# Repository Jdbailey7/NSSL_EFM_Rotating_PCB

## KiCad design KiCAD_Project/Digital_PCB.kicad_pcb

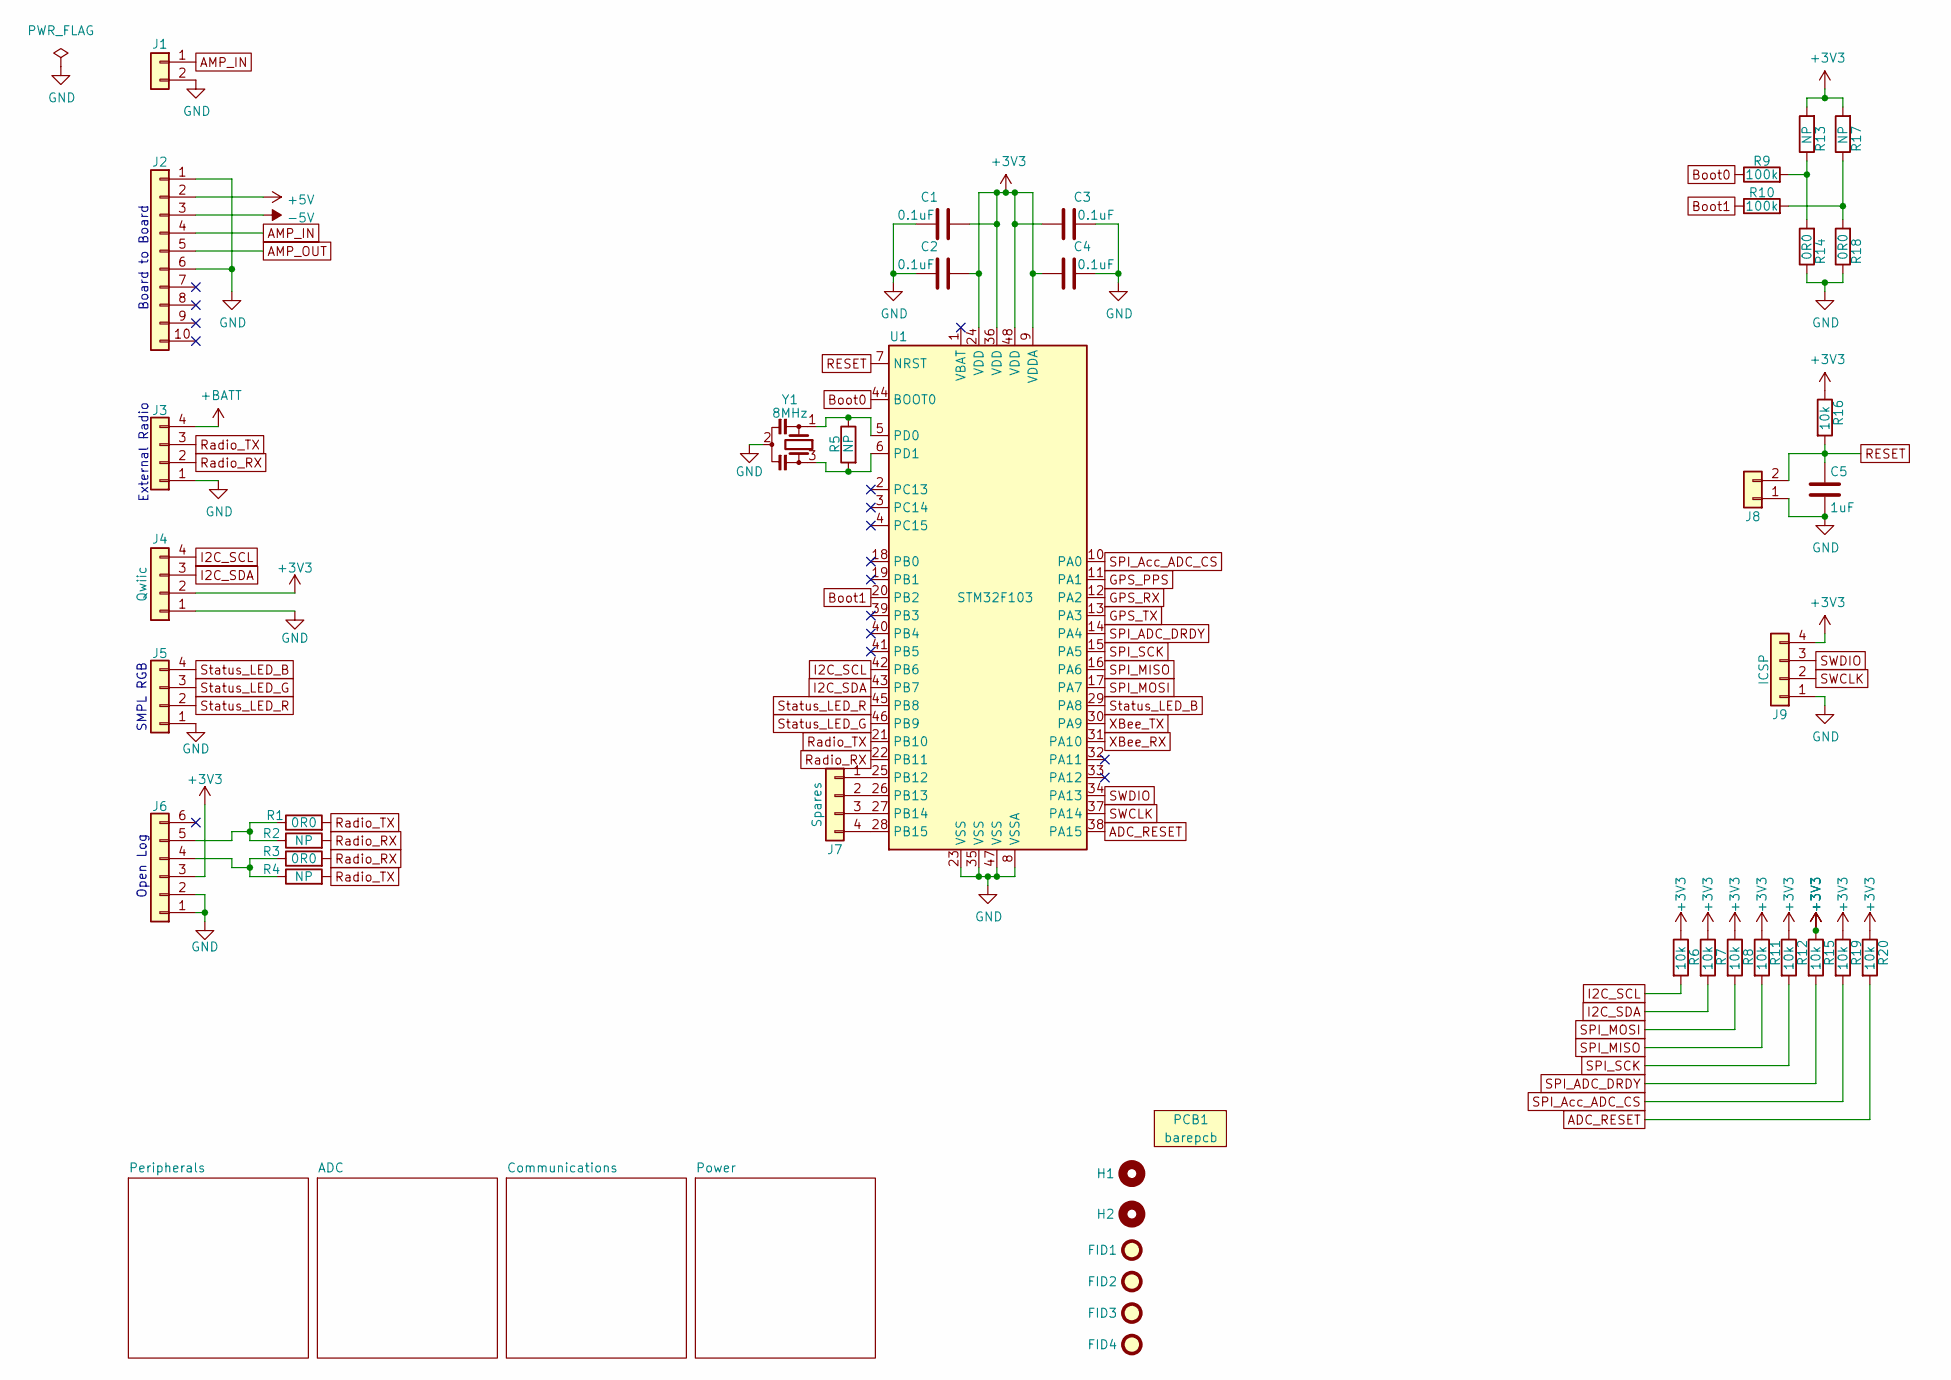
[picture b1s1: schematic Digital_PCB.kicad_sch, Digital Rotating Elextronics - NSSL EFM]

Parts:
C1, C2, C3, C4: 1-0000007
C5: 1-0000018
FID1, FID2, FID3, FID4: Fiducial_1mm_2mm; Fiducial_1mm_Mask2mm
H1, H2: Imperial6; MountingHole_imperial6
J1: NP_Conn_01x02_Relief; SolderWire_1x02_Relief
J2: Board to Board; PinHeader_1x10_P2.54mm_Vertical
J3, J5: 1-0001156
J4: 1-0001205
J6: NP_Conn_01x06; PinHeader_1x06_P2.54mm_Vertical
J7, J9: NP_Conn_01x04; PinHeader_1x04_P2.54mm_Vertical
J8: NP_Conn_01x02_Relief; PinHeader_1x02_P2.54mm_Vertical
PCB1: barepcb
R1, R2, R3, R4, R5, R13, R14, R17, R18: 1-0000006
R6, R7, R8, R11, R12, R15, R16, R19, R20: 1-0000010
R9, R10: 1-0000174
U1: 1-0000207
Y1: 1-0000721

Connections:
+3V3: C1.2, C2.2, C3.2, C4.2, J4.2, J6.3, J9.4, R6.1, R7.1, R8.1, R11.1, R12.1, R13.2, R15.1, R16.1, R17.2, R19.1, R20.1, U1.9 (VDDA), U1.24 (VDD), U1.36 (VDD), U1.48 (VDD); also elsewhere on the board
+5V: J2.2; also elsewhere on the board
+BATT: J3.4; also elsewhere on the board
-5V: J2.3; also elsewhere on the board
ADC_RESET: R20.2, U1.38 (PA15); also elsewhere on the board
AMP_IN: J1.1, J2.4
AMP_OUT: J2.5; also elsewhere on the board
Boot0: R9.1, U1.44 (BOOT0)
Boot1: R10.1, U1.20 (PB2)
GND: C1.1, C2.1, C3.1, C4.1, C5.2, J1.2, J2.1, J2.6, J3.1, J4.1, J5.1, J6.1, J6.2, J8.1, J9.1, R14.1, R18.1, U1.8 (VSSA), U1.23 (VSS), U1.35 (VSS), U1.47 (VSS), Y1.2; also elsewhere on the board
GPS_PPS: U1.11 (PA1); also elsewhere on the board
GPS_RX: U1.12 (PA2); also elsewhere on the board
GPS_TX: U1.13 (PA3); also elsewhere on the board
I2C_SCL: J4.4, R6.2, U1.42 (PB6); also elsewhere on the board
I2C_SDA: J4.3, R7.2, U1.43 (PB7); also elsewhere on the board
unnamed: J6.4, R3.1, R4.1
unnamed: J6.5, R1.1, R2.1
unnamed: J7.1, U1.25 (PB12)
unnamed: J7.2, U1.26 (PB13)
unnamed: J7.3, U1.27 (PB14)
unnamed: J7.4, U1.28 (PB15)
unnamed: R10.2, R17.1, R18.2
unnamed: R9.2, R13.1, R14.2
unnamed: R5.1, U1.5 (PD0), Y1.1
unnamed: R5.2, U1.6 (PD1), Y1.3
RESET: C5.1, J8.2, R16.2, U1.7 (NRST); also elsewhere on the board
Radio_RX: J3.2, R2.2, R3.2, U1.22 (PB11)
Radio_TX: J3.3, R1.2, R4.2, U1.21 (PB10)
SPI_ADC_DRDY: R15.2, U1.14 (PA4); also elsewhere on the board
SPI_Acc_ADC_CS: R19.2, U1.10 (PA0); also elsewhere on the board
SPI_MISO: R11.2, U1.16 (PA6); also elsewhere on the board
SPI_MOSI: R8.2, U1.17 (PA7); also elsewhere on the board
SPI_SCK: R12.2, U1.15 (PA5); also elsewhere on the board
SWCLK: J9.2, U1.37 (PA14)
SWDIO: J9.3, U1.34 (PA13)
Status_LED_B: J5.4, U1.29 (PA8)
Status_LED_G: J5.3, U1.46 (PB9)
Status_LED_R: J5.2, U1.45 (PB8)
XBee_RX: U1.31 (PA10); also elsewhere on the board
XBee_TX: U1.30 (PA9); also elsewhere on the board

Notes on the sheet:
Board to Board
External Radio
Open Log
SMPL RGB

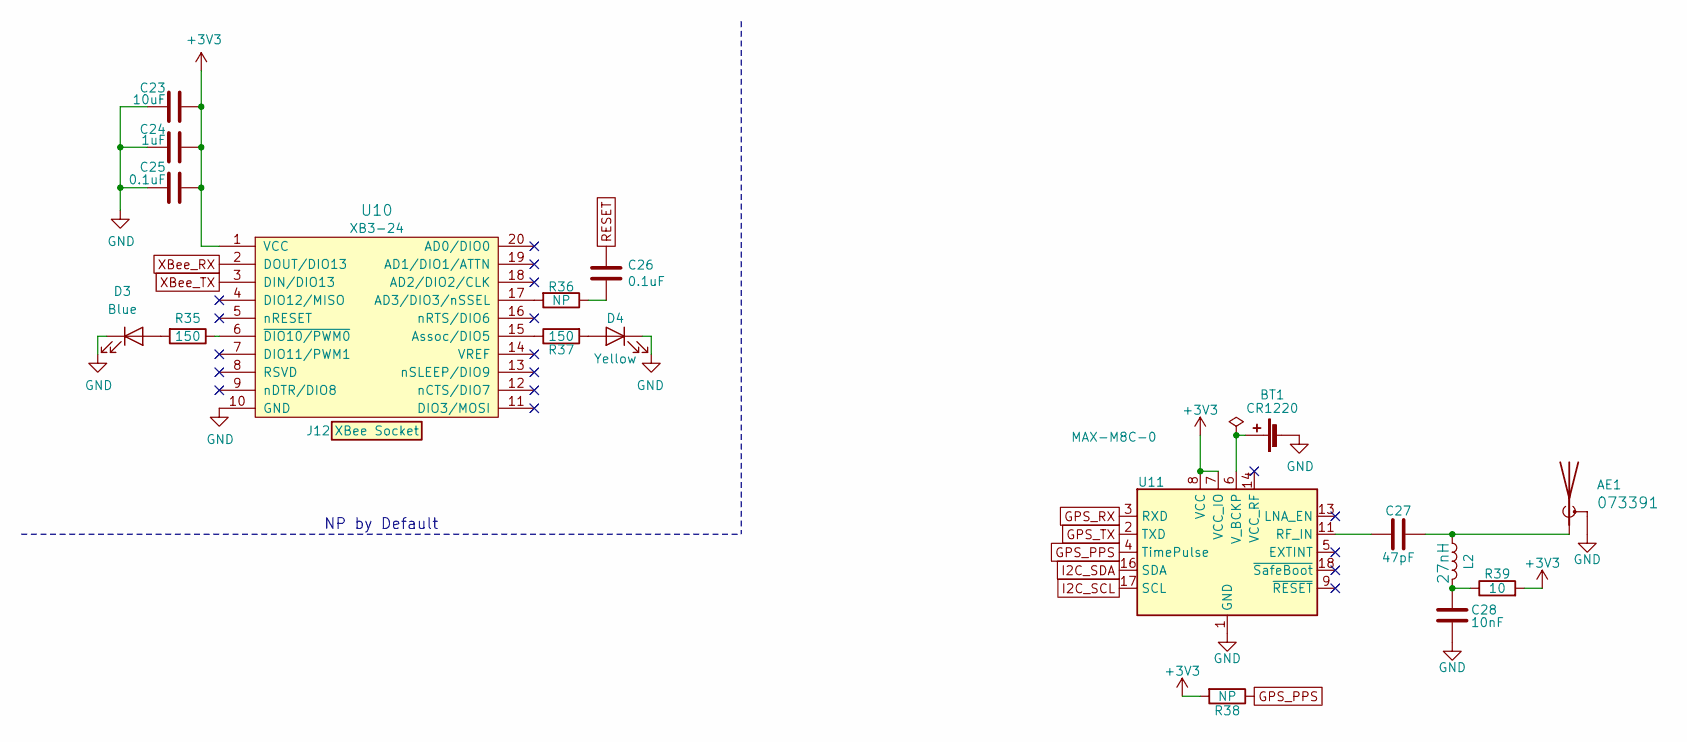
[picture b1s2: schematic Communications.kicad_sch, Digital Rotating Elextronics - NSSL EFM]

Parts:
AE1: 1-0000461
BT1: 1-0000246
C23: 1-0000075
C24: 1-0000018
C25, C26: 1-0000007
C27: 1-0000458
C28: 1-0000014
D3: 1-0000599
D4: 1-0000601
J12: 1-0000050
L2: 1-0000459
R35, R37: 1-0000008
R36: 1-0000006
R38: 1-0000010
R39: 1-0000678
U10: 1-0000785
U11: 1-0000464

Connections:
+3V3: C23.1, C24.1, C25.1, R38.2, R39.2, U10.1 (VCC), U11.7 (VCC_IO), U11.8 (VCC); also elsewhere on the board
GND: AE1.2 (Shield), BT1.2 (-), C23.2, C24.2, C25.2, C28.2, D3.1 (K), D4.1 (K), U10.10 (GND), U11.1 (GND), U11.10 (GND), U11.12 (GND); also elsewhere on the board
GPS_PPS: R38.1, U11.4 (TimePulse); also elsewhere on the board
GPS_RX: U11.3 (RXD); also elsewhere on the board
GPS_TX: U11.2 (TXD); also elsewhere on the board
I2C_SCL: U11.17 (SCL); also elsewhere on the board
I2C_SDA: U11.16 (SDA); also elsewhere on the board
unnamed: AE1.1 (A), C27.2, L2.1
unnamed: BT1.1 (+), U11.6 (V_BCKP)
unnamed: C26.2, R36.1
unnamed: C28.1, L2.2, R39.1
unnamed: D3.2 (A), R35.2
unnamed: D4.2 (A), R37.2
unnamed: R36.2, U10.17 (AD3/DIO3/nSSEL)
unnamed: R37.1, U10.15 (Assoc/DIO5)
unnamed: R35.1, U10.6 (~DIO10/PWM0)
unnamed: C27.1, U11.11 (RF_IN)
RESET: C26.1; also elsewhere on the board
XBee_RX: U10.2 (DOUT/DIO13); also elsewhere on the board
XBee_TX: U10.3 (DIN/DIO13); also elsewhere on the board

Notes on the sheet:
NP by Default

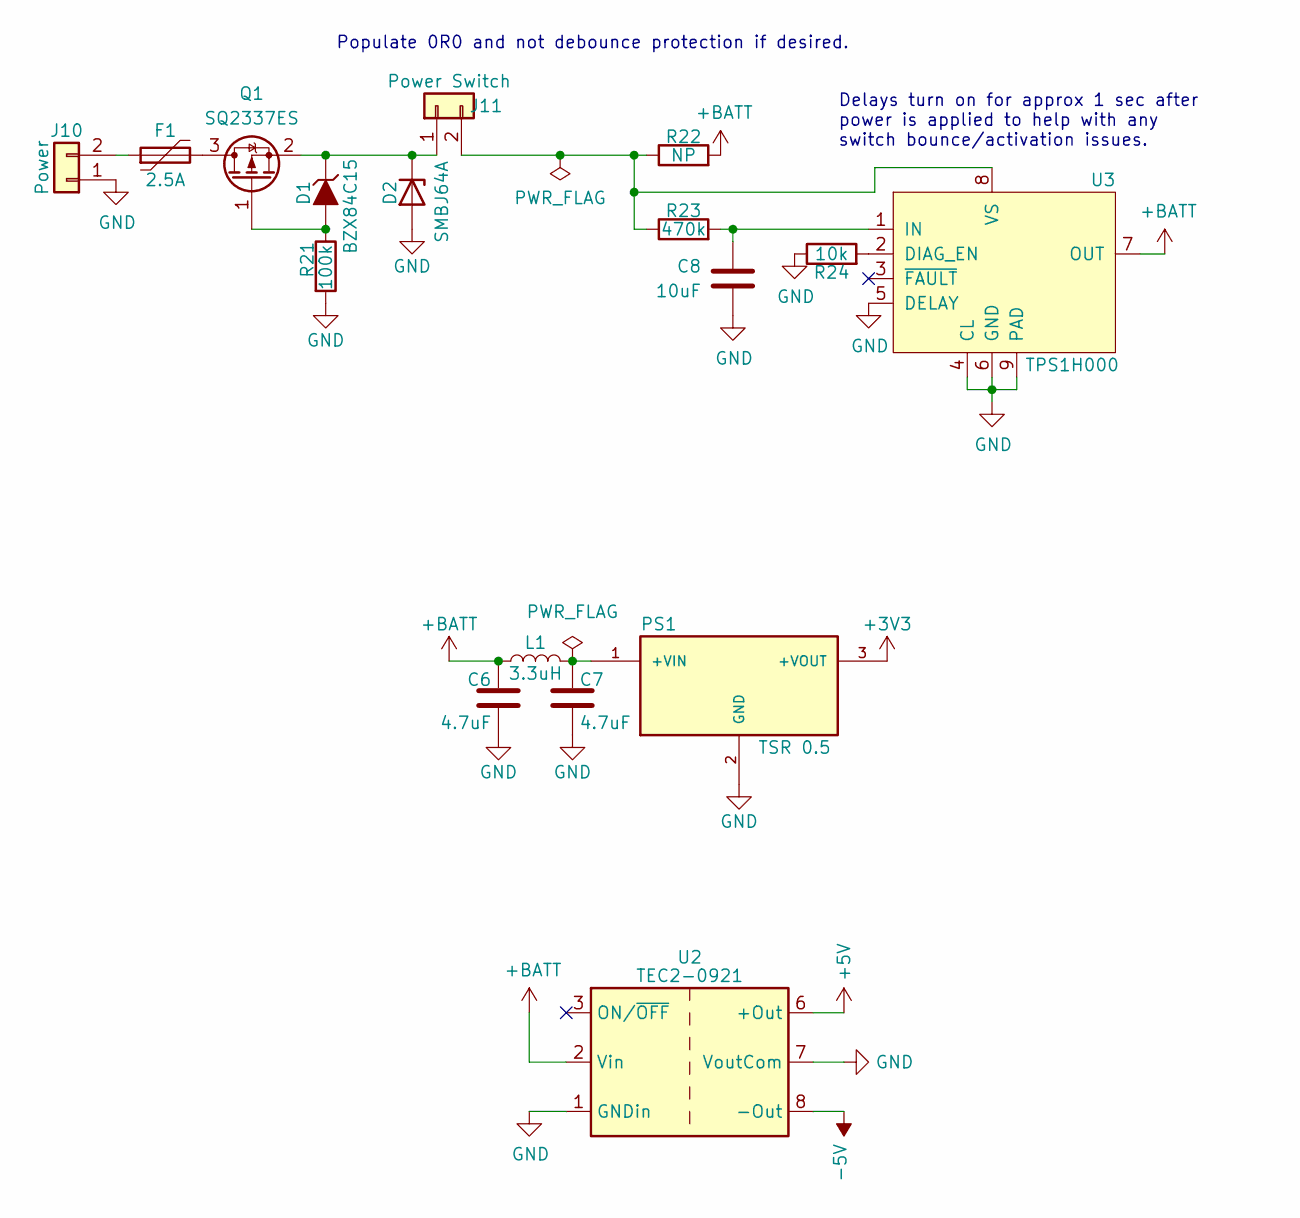
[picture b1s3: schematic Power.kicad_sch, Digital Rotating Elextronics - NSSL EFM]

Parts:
C6, C7: 1-0000136
C8: 1-0000075
D1: 1-0001672
D2: 1-0001537
F1: 1-0000269
J10, J11: NP_Conn_01x02_Relief; SolderWire_1x02_Relief
L1: 1-0000931
PS1: 1-0000727
Q1: 1-0001670
R21: 1-0000174
R22: 1-0000006
R23: 1-0000068
R24: 1-0000010
U2: 1-0000465
U3: 1-0000576

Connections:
+3V3: PS1.3 (+VOUT); also elsewhere on the board
+5V: U2.6 (+Out); also elsewhere on the board
+BATT: C6.1, L1.1, R22.2, U2.2 (Vin), U3.7 (OUT); also elsewhere on the board
-5V: U2.8 (-Out); also elsewhere on the board
GND: C6.2, C7.2, C8.1, D2.2 (A), J10.1, PS1.2 (GND), R21.2, R24.1, U2.1 (GNDin), U2.7 (VoutCom), U3.4 (CL), U3.5 (DELAY), U3.6 (GND), U3.9 (PAD); also elsewhere on the board
unnamed: D1.1 (A), Q1.1 (G), R21.1
unnamed: D1.3 (K), D2.1 (K), J11.1, Q1.2 (S)
unnamed: F1.1, J10.2
unnamed: J11.2, R22.1, R23.1, U3.8 (VS)
unnamed: C7.1, L1.2, PS1.1 (+VIN)
unnamed: F1.2, Q1.3 (D)
unnamed: R24.2, U3.2 (DIAG_EN)
unnamed: C8.2, R23.2, U3.1 (IN)

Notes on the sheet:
Populate 0R0 and not debounce protection if desired.
Delays turn on for approx 1 sec after power is applied to help with any switch bounce/activation issues.

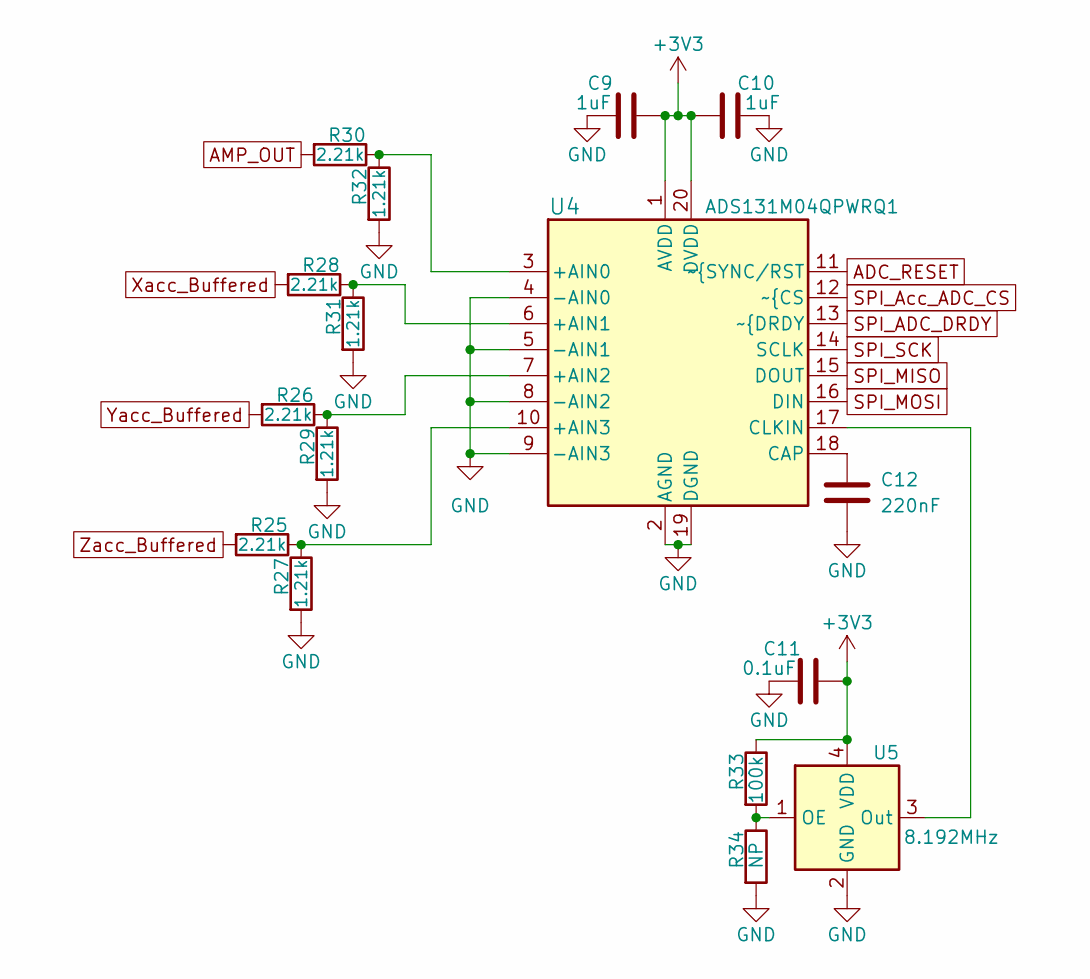
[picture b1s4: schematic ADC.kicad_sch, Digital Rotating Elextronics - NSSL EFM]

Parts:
C9, C10: 1-0000018
C11: 1-0000007
C12: 1-0000926
R25, R26, R28, R30: 1-0001551
R27, R29, R31, R32: 1-0001553
R33: 1-0000174
R34: 1-0000006
U4: 1-0001530
U5: 1-0001542

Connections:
+3V3: C9.1, C10.1, C11.2, R33.1, U4.1 (AVDD), U4.20 (DVDD), U5.4 (VDD); also elsewhere on the board
ADC_RESET: U4.11 (~{SYNC/RST); also elsewhere on the board
AMP_OUT: R30.2; also elsewhere on the board
GND: C9.2, C10.2, C11.1, C12.2, R27.2, R29.2, R31.2, R32.2, R34.2, U4.2 (AGND), U4.4 (-AIN0), U4.5 (-AIN1), U4.8 (-AIN2), U4.9 (-AIN3), U4.19 (DGND), U5.2 (GND); also elsewhere on the board
unnamed: R30.1, R32.1, U4.3 (+AIN0)
unnamed: R28.1, R31.1, U4.6 (+AIN1)
unnamed: R26.1, R29.1, U4.7 (+AIN2)
unnamed: R25.1, R27.1, U4.10 (+AIN3)
unnamed: C12.1, U4.18 (CAP)
unnamed: U4.17 (CLKIN), U5.3 (Out)
unnamed: R33.2, R34.1, U5.1 (OE)
SPI_ADC_DRDY: U4.13 (~{DRDY); also elsewhere on the board
SPI_Acc_ADC_CS: U4.12 (~{CS); also elsewhere on the board
SPI_MISO: U4.15 (DOUT); also elsewhere on the board
SPI_MOSI: U4.16 (DIN); also elsewhere on the board
SPI_SCK: U4.14 (SCLK); also elsewhere on the board
Xacc_Buffered: R28.2; also elsewhere on the board
Yacc_Buffered: R26.2; also elsewhere on the board
Zacc_Buffered: R25.2; also elsewhere on the board

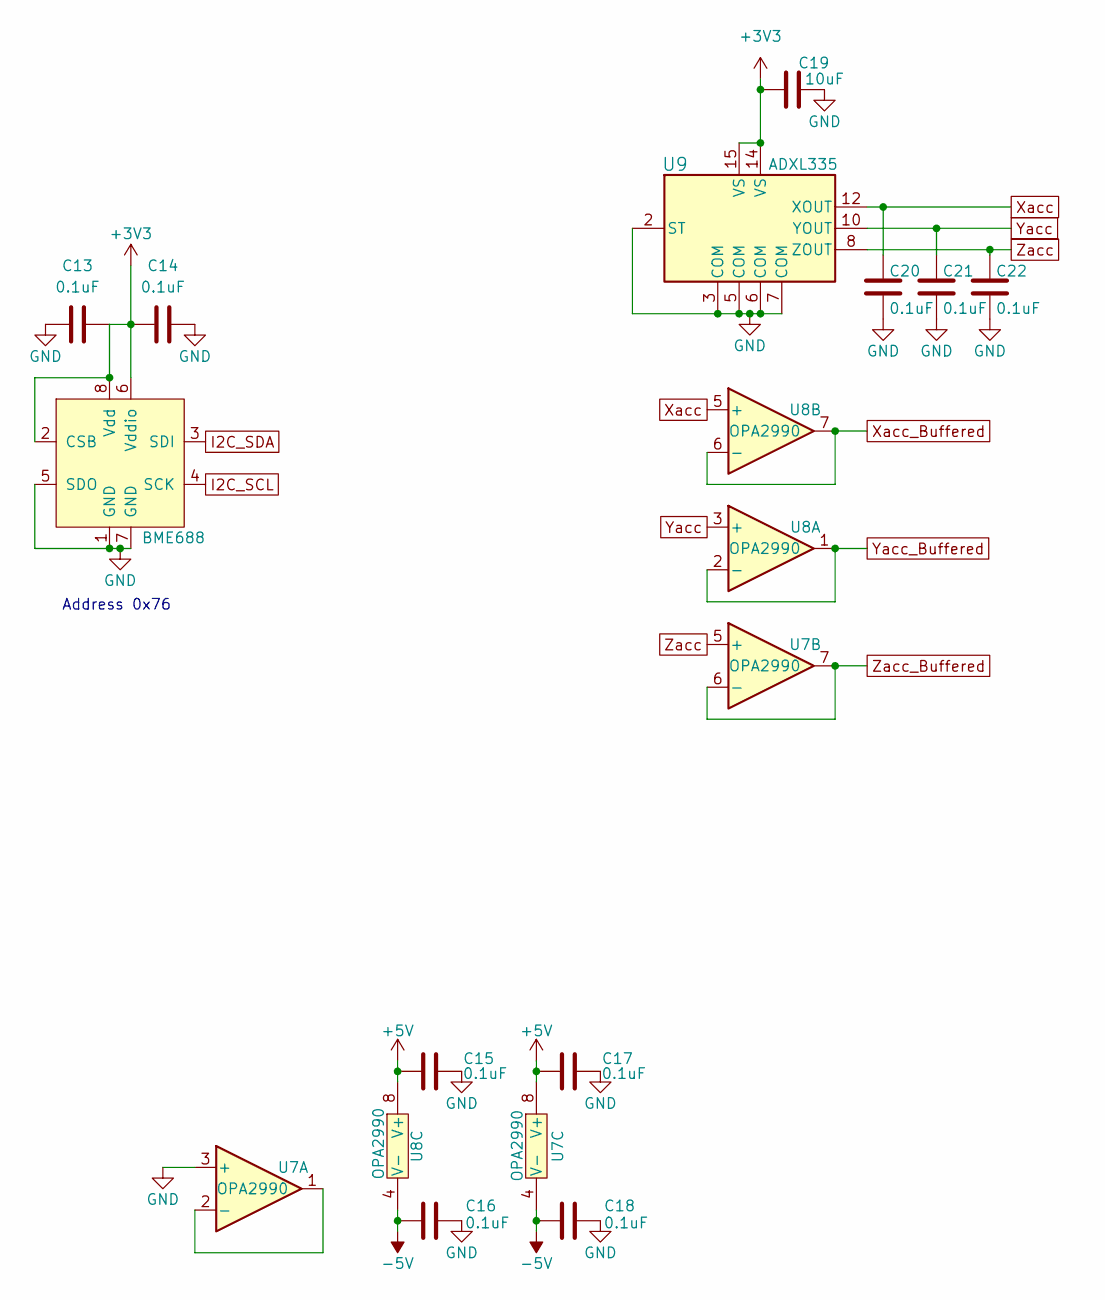
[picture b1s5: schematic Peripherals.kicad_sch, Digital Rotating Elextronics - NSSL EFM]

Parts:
C13, C14, C15, C16, C17, C18, C20, C21, C22: 1-0000007
C19: 1-0000075
U6: 1-0001471
U7, U8: 1-0000264
U9: 1-0001535

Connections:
+3V3: C13.2, C14.1, C19.1, U6.2 (CSB), U6.6 (Vddio), U6.8 (Vdd), U9.14 (VS), U9.15 (VS); also elsewhere on the board
+5V: C15.1, C17.1, U7.8 (V+), U8.8 (V+); also elsewhere on the board
-5V: C16.1, C18.1, U7.4 (V-), U8.4 (V-); also elsewhere on the board
GND: C13.1, C14.2, C15.2, C16.2, C17.2, C18.2, C19.2, C20.2, C21.2, C22.2, U6.1 (GND), U6.5 (SDO), U6.7 (GND), U7.3 (+), U9.2 (ST), U9.3 (COM), U9.5 (COM), U9.6 (COM), U9.7 (COM); also elsewhere on the board
I2C_SCL: U6.4 (SCK); also elsewhere on the board
I2C_SDA: U6.3 (SDI); also elsewhere on the board
unnamed: U7.1, U7.2 (-)
Xacc: C20.1, U8.5 (+), U9.12 (XOUT)
Xacc_Buffered: U8.6 (-), U8.7; also elsewhere on the board
Yacc: C21.1, U8.3 (+), U9.10 (YOUT)
Yacc_Buffered: U8.1, U8.2 (-); also elsewhere on the board
Zacc: C22.1, U7.5 (+), U9.8 (ZOUT)
Zacc_Buffered: U7.6 (-), U7.7; also elsewhere on the board

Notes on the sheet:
Address 0x76

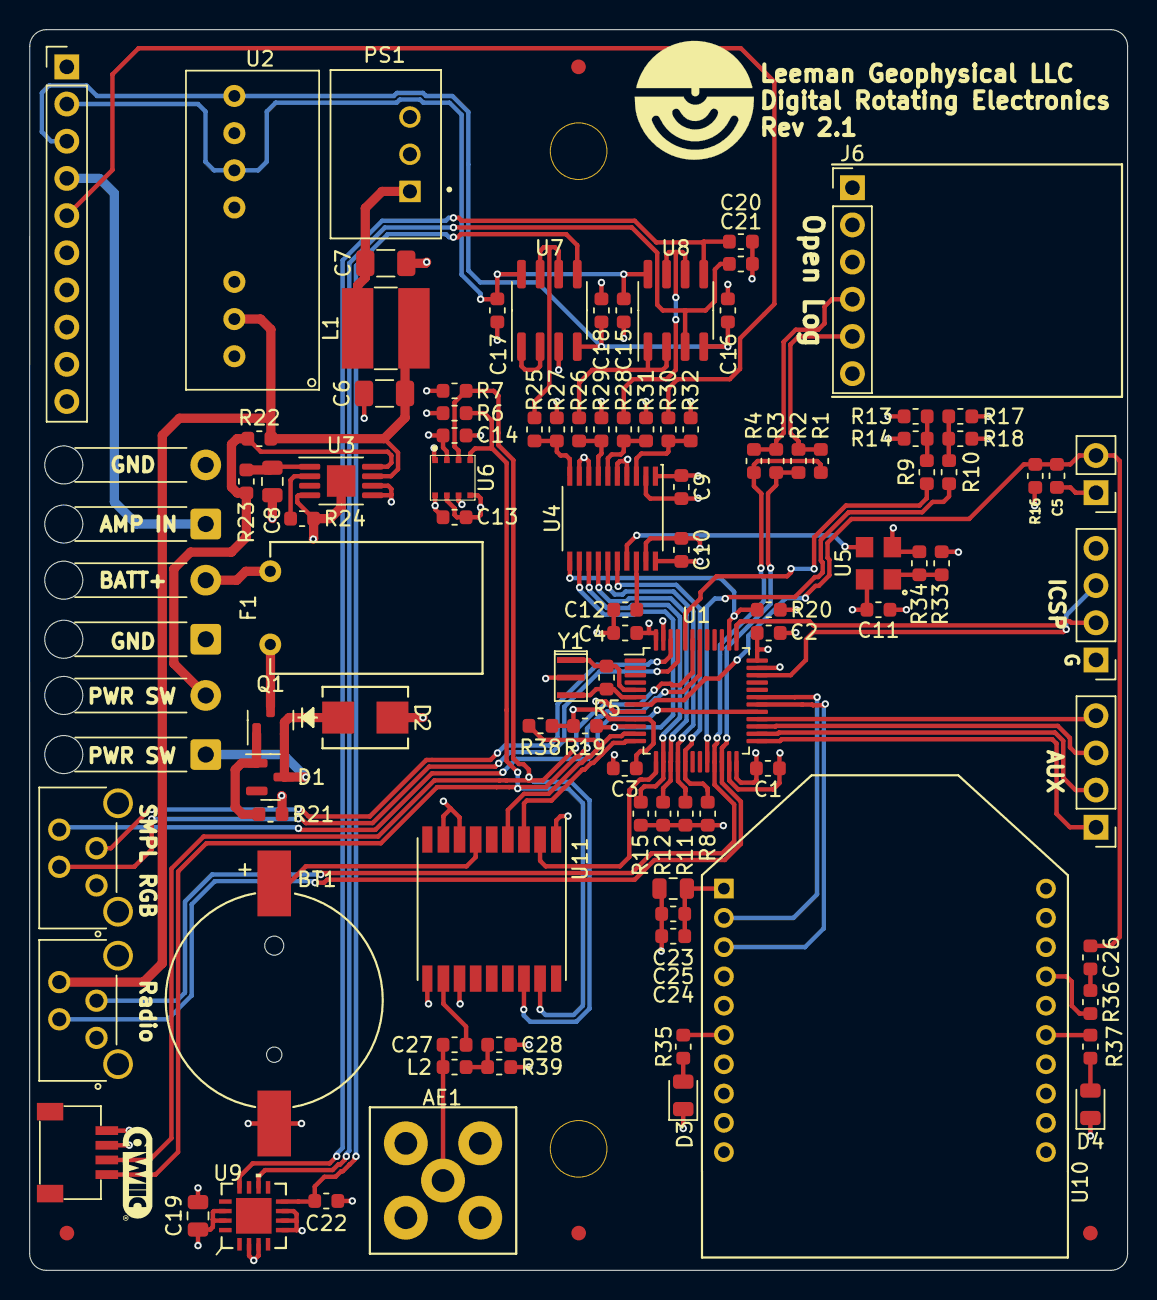
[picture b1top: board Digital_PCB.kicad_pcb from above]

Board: 4 copper layers, 75.0 x 84.8 mm, 109 parts (0 on the bottom side), 72 nets.

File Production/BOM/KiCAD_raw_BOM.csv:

"Reference","Internal Part Number","PValue","Populated"
"AE1","1-0000461","073391","1"
"BT1","1-0000246","CR1220","1"
"C1","1-0000007","0.1uF","1"
"C2","1-0000007","0.1uF","1"
"C3","1-0000007","0.1uF","1"
"C4","1-0000007","0.1uF","1"
"C5","1-0000018","1uF","1"
"C6","1-0000136","4.7uF","1"
"C7","1-0000136","4.7uF","1"
"C8","1-0000075","10uF","1"
"C9","1-0000018","1uF","1"
"C10","1-0000018","1uF","1"
"C11","1-0000007","0.1uF","1"
"C12","1-0000926","220nF","1"
"C13","1-0000007","0.1uF","1"
"C14","1-0000007","0.1uF","1"
"C15","1-0000007","0.1uF","1"
"C16","1-0000007","0.1uF","1"
"C17","1-0000007","0.1uF","1"
"C18","1-0000007","0.1uF","1"
"C19","1-0000075","10uF","1"
"C20","1-0000007","0.1uF","1"
"C21","1-0000007","0.1uF","1"
"C22","1-0000007","0.1uF","1"
"C23","1-0000075","10uF","0"
"C24","1-0000018","1uF","0"
"C25","1-0000007","0.1uF","0"
"C26","1-0000007","0.1uF","0"
"C27","1-0000458","47pF","1"
"C28","1-0000014","10nF","1"
"D1","1-0001672","BZX84C15","1"
"D2","1-0001537","SMBJ64A","1"
"D3","1-0000599","Blue","0"
"D4","1-0000601","Yellow","0"
"F1","1-0000269","2.5A","1"
"FID1","0-0000000","Fiducial","0"
"FID2","0-0000000","Fiducial","0"
"FID3","0-0000000","Fiducial","0"
"FID4","0-0000000","Fiducial","0"
"H1","0-0000000","M3","0"
"H2","0-0000000","M3","0"
"J1","0-0000000","NP_Conn_01x02","0"
"J2","1-0000455","","1"
"J3","1-0001156","4 Pos","1"
"J4","1-0001205","Qwiic","1"
"J5","1-0001156","4 Pos","1"
"J6","0-0000000","01x06","0"
"J7","0-0000000","Spares","0"
"J8","0-0000000","NP_Conn_01x02","0"
"J9","0-0000000","ICSP","0"
"J10","0-0000000","Power","0"
"J11","0-0000000","Power Switch","0"
"J12","1-0000050","XBee Socket","0"
"L1","1-0000931","3.3uH","1"
"L2","1-0000459","27nH","1"
"PCB1","3-0000279","Bare PCB","1"
"PS1","1-0000727","TSR 0.5","1"
"Q1","1-0001670","SQ2337ES","1"
"R1","1-0000006","0R0","1"
"R2","1-0000006","NP","0"
"R3","1-0000006","0R0","1"
"R4","1-0000006","NP","0"
"R5","1-0000006","NP","0"
"R6","1-0000010","10k","1"
"R7","1-0000010","10k","1"
"R8","1-0000010","10k","1"
"R9","1-0000174","100k","1"
"R10","1-0000174","100k","1"
"R11","1-0000010","10k","1"
"R12","1-0000010","10k","1"
"R13","1-0000006","NP","0"
"R14","1-0000006","0R0","1"
"R15","1-0000010","10k","1"
"R16","1-0000010","10k","1"
"R17","1-0000006","NP","0"
"R18","1-0000006","0R0","1"
"R19","1-0000010","10k","1"
"R20","1-0000010","10k","1"
"R21","1-0000174","100k","1"
"R22","1-0000006","NP","0"
"R23","1-0000068","470k","1"
"R24","1-0000010","10k","1"
"R25","1-0001551","2.21k","1"
"R26","1-0001551","2.21k","1"
"R27","1-0001553","1.21k","1"
"R28","1-0001551","2.21k","1"
"R29","1-0001553","1.21k","1"
"R30","1-0001551","2.21k","1"
"R31","1-0001553","1.21k","1"
"R32","1-0001553","1.21k","1"
"R33","1-0000174","100k","1"
"R34","1-0000006","NP","0"
"R35","1-0000008","150","0"
"R36","1-0000006","NP","0"
"R37","1-0000008","150","0"
"R38","1-0000010","NP","1"
"R39","1-0000678","10","1"
"U1","1-0000207","STM32F103","1"
"U2","1-0000465","TEC2-0921","1"
"U3","1-0000576","TPS1H000","1"
"U4","1-0001530","ADS131M04QPWRQ1","1"
"U5","1-0001542","8.192MHz","1"
"U6","1-0001471","BME688","1"
"U7","1-0000264","OPA2990","1"
"U8","1-0000264","OPA2990","1"
"U9","1-0001535","ADXL335","1"
"U10","1-0000785","XB3-24","1"
"U11","1-0000464","MAX-M8C-0","1"
"Y1","1-0000721","8MHz","1"

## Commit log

2025-09-12 Rev 2.1 Changes: - Fixed Issue #11 (U4 Footprint pin 1 indicator) - Added Open Log Header for breakout - Removed SD Circuit - Connected GPS to I2C - Updated IPN and Revision Number
2026-02-13 Make Rev 2.1 production files
